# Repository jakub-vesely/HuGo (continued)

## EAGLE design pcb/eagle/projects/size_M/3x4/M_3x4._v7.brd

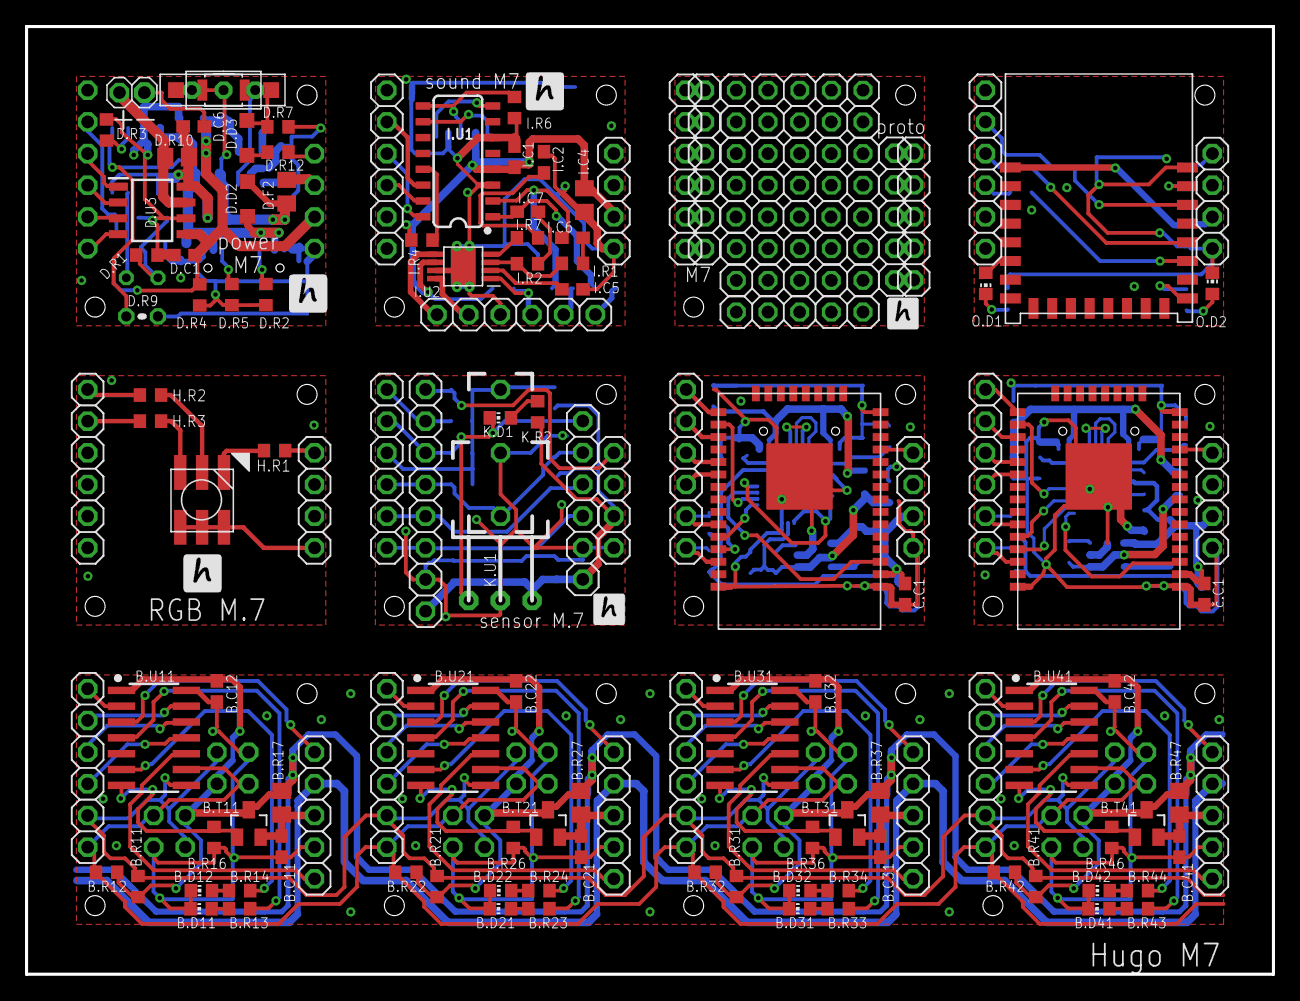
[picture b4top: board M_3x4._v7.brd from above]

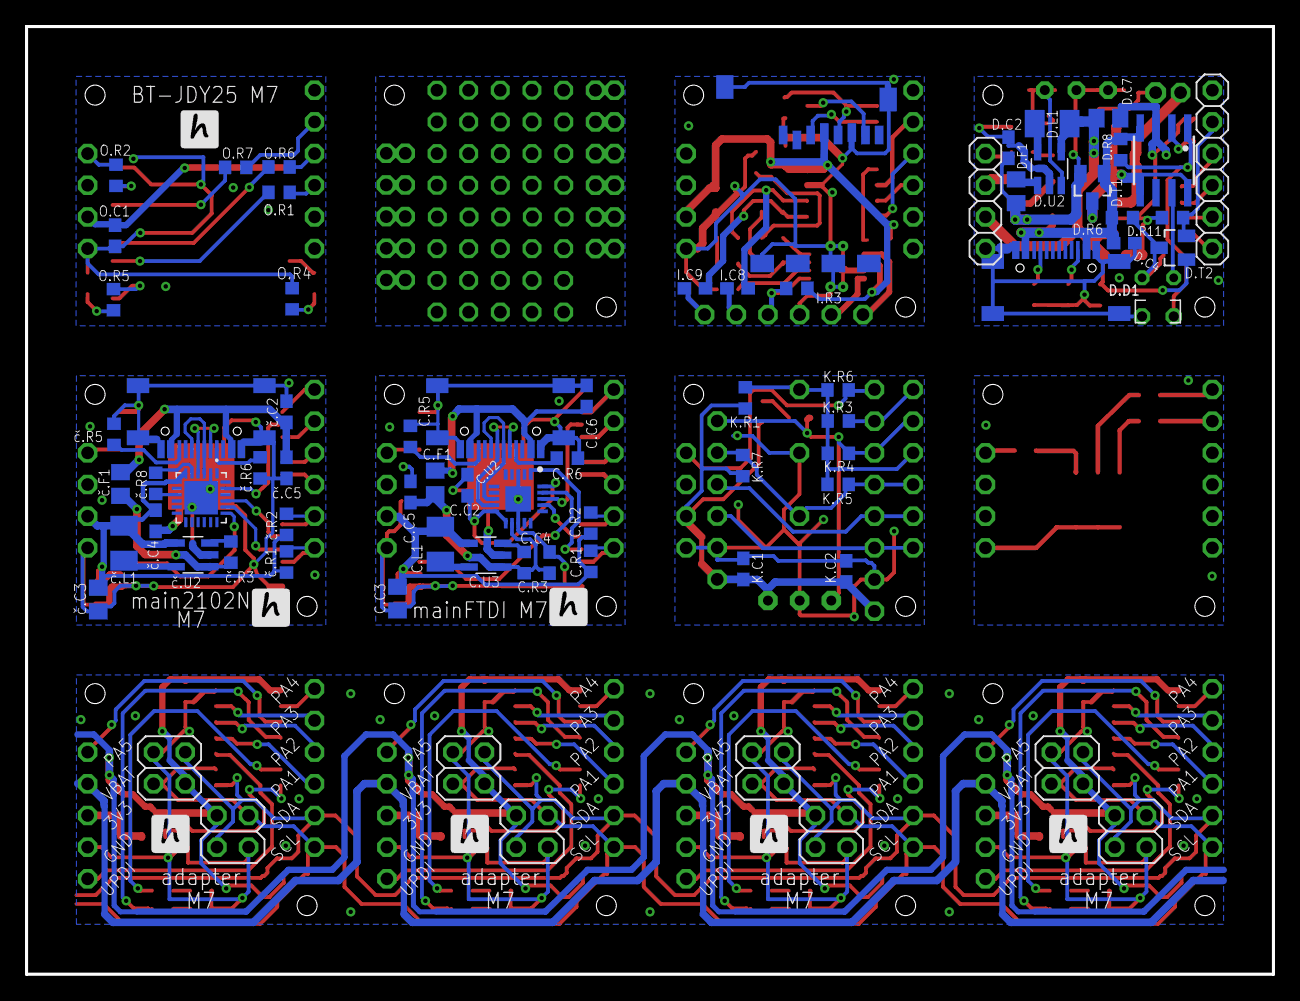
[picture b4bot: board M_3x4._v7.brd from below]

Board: 2 copper layers, 100.0 x 76.0 mm, 201 parts (73 on the bottom side), 185 nets.

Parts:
B.C11, B.C12, B.C21, B.C22, B.C31, B.C32, B.C41, B.C42: 100n; C0603
B.D11, B.D12, B.D21, B.D22, B.D31, B.D32, B.D41, B.D42: CHIP-LED0603
B.J1, B.J8, B.J12, B.J16: 1X05
B.J2, B.J5, B.J9, B.J13: 1X06
B.J3, B.J4, B.J6, B.J7, B.J10, B.J11, B.J14, B.J15: 2X02
B.R11, B.R12, B.R21, B.R22, B.R31, B.R32, B.R41, B.R42: 2k2; R0603
B.R13, B.R14, B.R23, B.R24, B.R33, B.R34, B.R43, B.R44: 1k; R0603
B.R16, B.R26, B.R36, B.R46: 100k; R0603
B.R17, B.R27, B.R37, B.R47: alt fuse or 0R; FUSE
B.T11, B.T21, B.T31, B.T41: NX3008; SO23
B.U11, B.U21, B.U31, B.U41: AT414; SO14
C.C1, C.C2, C.C4: 100n; C0603
C.C3: 22u; C0805
C.C5: 4u7; C0603
C.C6: 10nF; C0603
C.F1: 0.5A; R0805
C.J1, C.J2: 1X06
C.L1: 4u7; L3230M
C.R1, C.R2: 2k2; R0603
C.R3: 100k; R0603
C.R5: 5K1; R0603
C.R6: 5k1; R0603
C.U1, C.U4: TTGO-MICRO-32
C.U2: FT231XQ-R; QFN50P400X400X80-21N
C.U3: MCP1603T-330I; SOT32-5
D.C1: 100n; C0603
D.C2, D.C4, D.C6: 4u7; C0603
D.C7: 10u; C0805
D.D1: LED_1.8
D.D2, D.D3: SHOTKY_2.8
D.F1: 0.5A; R0805
D.F2: 1.1A; R0805
D.J2: 1X06
D.J3: 1X04
D.L1: 2u2; L3230M
D.LIPOL: 1X02-2
D.ON/OFF/RESET: SWITCH
D.R1, D.R2, D.R5: 5k1; R0603
D.R3: I=1800/R (10k for 0.2A, 3k3 for 0.55A, 3k9 for 0.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; R0603
D.R4, D.R7, D.R11: 390k; R0603
D.R6: 3k3; R0603
D.R8: 10k?; R0603
D.R9: TERM_10K; THERM
D.R10: 0.1; R0805
D.R12: 100k; R0603
D.T1: FDV304; SO23
D.T2: NX3008; SO23
D.U2: LM3671_3.3; SOT32-5
D.U3: INA219AIDR; SOIC127P600X175-8N
G.J1: 1X06
G.J2: 1X04
H.D1: RGB_WW-FCE50TC-Q1
H.J2, H.J4: 1X06
H.R1, H.R2, H.R3: 82; R0603
I.C1, I.C2, I.C6, I.C7, I.C8, I.C9: 100n; C0603
I.C4: 10u (22u); C0805
I.C5: 220n; C0603
I.J1, I.J3: 1X04
I.J2: 1X06
I.R1, I.R2, I.R3, I.R4, I.R7: 10k; R0603
I.R6: 1k5; R0603
I.U1: WT2003S; SO16
I.U2: TPA6211; MSOP-POWERPAD-8
JP1, JP2, JP3: 1X04
JP4, JP5, JP7, JP9: 1X06
JP6, JP11: 1X05
JP8: 1X08
K.C1, K.C2: C0603
K.D1: CHIP-LED0603
K.R1, K.R7: 100K; R0603
K.R2: 180R; R0603
K.R3, K.R4, K.R5, K.R6: 0R; R0603
K.U1: VS1838B; IR_RECEIVER
O.C1: 100n; C0603
O.D1, O.D2: CHIP-LED0603
O.R1, O.R2, O.R4, O.R5, O.R6, O.R7: 2k2; R0603
U$1, U$2, U$3: USB-C
U$4: CN3083; SOP8
U$5: MICRO_SD; MOCRO_SD
U$6, U$7, U$8, U$9, U$10, U$11, U$12, U$13: PINHD-1X5_AUTO; 1X5_AUTO
U$14: JDY-25
U$15: BUTTON-SWITCH
č.C1, č.C2, č.C4: 100n; C0603
č.C3: 22u; C0805
č.C5: 4u7; C0603
č.F1: 0.5A; R0805
č.L1: 4u7; L3230M
č.R1, č.R2: 2k2; R0603
č.R3, č.R8: 100k; R0603
č.R5: 5K1; R0603
č.R6: 5k1; R0603
č.U1: CP2102N; QFN50P400X400X80-25N
č.U2: MCP1603T-330I; SOT32-5

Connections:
GND: B.C11.2, B.C12.2, B.C21.2, B.C22.2, B.C31.2, B.C32.2, B.C41.2, B.C42.2, B.D11.C1, B.D12.C1, B.D21.C1, B.D22.C1, B.D31.C1, B.D32.C1, B.D41.C1, B.D42.C1, B.J1.4, B.J3.4, B.J4.1, B.J6.4, B.J7.1, B.J8.4, B.J10.4, B.J11.1, B.J12.4, B.J14.4, B.J15.1, B.J16.4, B.R16.2, B.R26.2, B.R36.2, B.R46.2, B.U11.14, B.U21.14, B.U31.14, B.U41.14
GND1: C.C1.2, C.C2.2, C.C3.2, C.C4.2, C.C5.1, C.C6.1, C.R5.1, C.R6.1, C.U1.GND1, C.U1.GND2, C.U1.GND3, C.U1.GND4, C.U1.GND5, C.U1.GND6, C.U1.GND7, C.U1.GND8, C.U1.GND9, C.U1.GND10, C.U1.GND11, C.U2.3, C.U2.13, C.U2.21, C.U3.GND, JP1.4, U$1.A1B12, U$1.B1A12, U$1.SH1, U$1.SH2, U$1.SH3, U$1.SH4
GND2: C.U4.GND1, C.U4.GND2, C.U4.GND3, C.U4.GND4, C.U4.GND5, C.U4.GND6, C.U4.GND7, C.U4.GND8, C.U4.GND9, C.U4.GND10, C.U4.GND11, JP2.4, U$2.A1B12, U$2.B1A12, U$2.SH1, U$2.SH2, U$2.SH3, U$2.SH4, č.C1.2, č.C2.2, č.C3.2, č.C4.2, č.C5.1, č.R5.1, č.R6.1, č.U1.2, č.U1.25, č.U2.GND
GND3: D.C1.1, D.C2.1, D.C4.1, D.C6.1, D.C7.1, D.J3.4, D.LIPOL.1, D.R1.1, D.R2.2, D.R3.1, D.R4.2, D.R5.2, D.R7.2, D.R9.1, D.R11.2, D.U2.GND, D.U3.6, U$3.A1B12, U$3.B1A12, U$3.SH1, U$3.SH2, U$3.SH3, U$3.SH4, U$4.3
GND4: H.D1.4, H.D1.5, H.D1.6, JP3.4
GND5: H.J4.4, I.C1.2, I.C2.1, I.C4.1, I.C5.1, I.J3.4, I.R6.1, I.U1.3, I.U1.6, I.U2.7, I.U2.9, I.U2.P$10, I.U2.P$11, I.U2.P$12, I.U2.P$13, U$5.6, U$5.G1, U$5.G2, U$5.G3, U$5.G4
GND6: JP6.4, JP11.4
GND7: G.J2.4, O.C1.1, O.D2.C1, O.R4.1, U$14.GND
GND8: I.J1.4, JP8.2, JP9.2, K.C1.2, K.C2.2, K.U1.GND, U$15.P$2
IN+: D.LIPOL.2, D.R10.2, D.U3.7
IN-: D.C6.2, D.R10.1, D.T1.D, D.U3.8, U$4.5, U$4.8
unnamed: B.C21.1, B.J8.3, B.R27.1, B.T21.S
unnamed: B.D22.A1, B.R24.1
unnamed: B.D12.A1, B.R14.1
unnamed: B.C11.1, B.J1.3, B.R17.1, B.T11.S
unnamed: B.R13.2, B.U11.4
unnamed: B.R23.2, B.U21.4
unnamed: B.C31.1, B.J12.3, B.R37.1, B.T31.S
unnamed: B.D32.A1, B.R34.1
unnamed: B.R33.2, B.U31.4
unnamed: B.C41.1, B.J16.3, B.R47.1, B.T41.S
unnamed: B.D42.A1, B.R44.1
unnamed: B.R43.2, B.U41.4
unnamed: C.U2.9, U$1.A7, U$1.B7
unnamed: C.U2.8, U$1.A6, U$1.B6
unnamed: C.R6.2, U$1.A5
unnamed: C.R5.2, U$1.B5
unnamed: C.L1.1, C.U3.VOUT
unnamed: C.R3.1, C.U3.SHDN
unnamed: C.C2.1, C.U2.10, C.U2.11, C.U2.20
unnamed: C.C6.2, C.F1.1, U$1.A4B9, U$1.B4A9
unnamed: U$2.A7, U$2.B7, č.U1.4
unnamed: U$2.A6, U$2.B6, č.U1.3
unnamed: U$2.A5, č.R6.2
unnamed: U$2.B5, č.R5.2
unnamed: č.R8.2, č.U1.5
unnamed: č.L1.1, č.U2.VOUT
unnamed: č.R3.1, č.U2.SHDN
unnamed: C.J1.5, C.U4.IO4
unnamed: C.J1.4, C.U4.IO17
unnamed: C.J1.3, C.U4.IO5
unnamed: C.J1.6, C.U4.IO2
unnamed: C.U4.IO27, JP2.1
unnamed: č.R8.1, č.U1.9
unnamed: č.F1.2, č.R3.2, č.U2.VIN
unnamed: D.L1.1, D.U2.VOUT
unnamed: D.R5.1, U$3.B5
unnamed: D.R2.1, U$3.A5
unnamed: D.R3.2, U$4.2
unnamed: D.D1.1, U$4.7
unnamed: D.R8.1, D.R9.2, U$4.1
unnamed: D.F1.2, D.U2.VIN
unnamed: D.D3.K, D.ON/OFF/RESET.P$1, D.ON/OFF/RESET.P$5, D.ON/OFF/RESET.P$7, D.R7.1, D.U2.SHDN
unnamed: D.D3.A, D.R12.2
unnamed: H.D1.2, H.R2.2
unnamed: H.D1.1, H.R1.2
unnamed: H.D1.3, H.R3.2
unnamed: H.R1.1, JP3.1
unnamed: H.J2.6, H.R2.1
unnamed: H.J2.5, H.R3.1
unnamed: I.C6.1, I.C8.1, I.U1.2
unnamed: I.C7.1, I.C9.1, I.U1.1
unnamed: I.C5.2, I.U2.2
unnamed: I.R1.2, I.R2.2, I.U2.3
unnamed: I.C6.2, I.R1.1
unnamed: I.C7.2, I.R2.1
unnamed: I.C2.2, I.R7.1
unnamed: I.R7.2, I.U2.4
unnamed: I.R4.2, I.U1.13
unnamed: I.J2.5, I.U1.14
unnamed: JP4.5, JP5.5
unnamed: JP4.4, JP5.4
unnamed: JP4.3, JP5.3
unnamed: JP4.2, JP5.2
unnamed: JP4.1, JP5.1
unnamed: JP6.5, JP11.5
unnamed: JP6.2, JP11.2
unnamed: JP6.1, JP11.1
unnamed: JP6.3, JP11.3
unnamed: JP4.6, JP5.6
unnamed: G.J2.1, O.R2.1
unnamed: O.R1.1, U$14.RXD
unnamed: O.R6.1, U$14.TXD
unnamed: G.J1.5, O.R7.2
unnamed: O.R7.1, U$14.PWRC
unnamed: O.D2.A1, O.R5.1
unnamed: O.R5.2, U$14.ALED
unnamed: O.D1.A1, U$14.STAT
unnamed: O.D1.C1, O.R4.2
unnamed: O.R2.2, U$14.RST
unnamed: JP7.2, JP8.4, JP9.4
unnamed: JP7.1, JP8.3, JP9.3
unnamed: K.D1.A1, K.R2.2
unnamed: JP7.6, JP8.7, K.R3.2
unnamed: I.J1.1, JP8.8, K.R6.2
unnamed: JP7.5, JP8.6, JP9.6, K.D1.C1, K.R4.2, K.U1.OUT
unnamed: JP7.4, K.R1.2, K.R3.1, K.R4.1, K.R5.1, K.R6.1, U$15.P$3
unnamed: JP7.3, JP8.5, JP9.5, K.R5.2, K.R7.2, U$15.P$1
PA1: B.J2.3, B.U11.11
PA2: B.J2.4, B.U11.12
PA3: B.J2.5, B.U11.13
PA3-1: D.J2.5, D.R11.1, D.T2.S
PA4: B.J2.6, B.U11.2
PA5: B.J1.1, B.U11.3
PA5-1: D.J3.1, D.R12.1
PA6: B.J5.5, B.U21.13
PA7: B.J5.4, B.U21.12
PA8: B.D21.A1, B.R23.1
PA9: B.J5.6, B.U21.2
PA10: B.J5.3, B.U21.11
PA11: B.J8.1, B.U21.3
PA12: B.J9.5, B.U31.13
PA13: B.J9.4, B.U31.12
PA14: B.D31.A1, B.R33.1
PA15: B.J9.6, B.U31.2
PA16: B.J9.3, B.U31.11
PA17: B.J12.1, B.U31.3
PA18: B.J13.5, B.U41.13
PA19: B.J13.4, B.U41.12
PA20: B.D41.A1, B.R43.1
PA21: B.J13.6, B.U41.2
PA22: B.J13.3, B.U41.11
PA23: B.J16.1, B.U41.3
PA24: C.J2.5, C.U1.IO4
PA25: C.J2.4, C.U1.IO17
PA26: C.J2.3, C.U1.IO5
PA27: C.J2.6, C.U1.IO2
PA28: C.U1.IO27, JP1.1
PA29: D.C4.2, D.D2.A, D.R6.2, D.R8.2, D.T1.G, U$3.A4B9, U$3.B4A9, U$4.4
PA30: D.J2.4, D.U3.1
PA31: D.J2.3, D.U3.2
PA32: D.D1.2, D.R1.2, D.R6.1, D.T2.D
PA51: B.D11.A1, B.R13.1
PB1: B.R26.1, B.T21.G, B.U21.7
PB2: B.R16.1, B.T11.G, B.U11.7
PB3: B.R14.2, B.U11.6
PB4: B.R24.2, B.U21.6
PB5: B.R36.1, B.T31.G, B.U31.7
PB6: B.R34.2, B.U31.6
PB7: B.R46.1, B.T41.G, B.U41.7
PB8: B.R44.2, B.U41.6
PROG: C.U1.IO0, C.U2.18
PROG1: C.U4.IO0, č.U1.23
RESET: C.U1.EN, C.U2.19
RESET1: C.U4.EN, č.U1.19
RX: C.U4.TXD0, č.U1.20
RX1: I.J2.3, I.U1.15
RX2: G.J1.3, O.R6.2
RX/TX: C.U1.TXD0, C.U2.1
SCL: B.J2.1, B.J3.2, B.J4.3, B.J5.1, B.J6.2, B.J7.3, B.J9.1, B.J10.2, B.J11.3, B.J13.1, B.J14.2, B.J15.3, B.R12.1, B.R22.1, B.R32.1, B.R42.1, B.U11.9, B.U21.9, B.U31.9, B.U41.9
SCL1: C.J2.1, C.R1.1, C.U1.IO22
SCL2: C.J1.1, C.U4.IO22, č.R1.1
SCL3: D.J2.1, D.U3.4
SDA: B.J2.2, B.J3.3, B.J4.2, B.J5.2, B.J6.3, B.J7.2, B.J9.2, B.J10.3, B.J11.2, B.J13.2, B.J14.3, B.J15.2, B.R11.1, B.R21.1, B.R31.1, B.R41.1, B.U11.8, B.U21.8, B.U31.8, B.U41.8
SDA1: C.J2.2, C.R2.1, C.U1.IO21
SDA2: C.J1.2, C.U4.IO21, č.R2.1
SDA3: D.J2.2, D.U3.3
SDCLK: I.R6.2, I.U1.9, U$5.5
SDCMD: I.U1.10, U$5.3
SDDAT: I.U1.8, U$5.7
SHTDOWN: H.J4.3, I.R3.1, I.U2.1
TX: C.U4.RXD0, č.U1.21
TX1: I.J2.4, I.U1.16
TX2: G.J1.4, O.R1.2
TX/RX: C.U1.RXD0, C.U2.17
UPDI: B.J1.5, B.U11.10
UPDI1: B.J8.5, B.U21.10
UPDI2: B.J12.5, B.U31.10
UPDI3: B.J16.5, B.U41.10
VBAT: B.J1.2, B.J8.2, B.J12.2, B.J16.2
VBATF: D.F2.2, D.J3.2
VCC: B.C12.1, B.C22.1, B.C32.1, B.C42.1, B.J3.1, B.J4.4, B.J6.1, B.J7.4, B.J10.1, B.J11.4, B.J14.1, B.J15.4, B.R11.2, B.R12.2, B.R17.2, B.R21.2, B.R22.2, B.R27.2, B.R31.2, B.R32.2, B.R37.2, B.R41.2, B.R42.2, B.R47.2, B.T11.D, B.T21.D, B.T31.D, B.T41.D, B.U11.1, B.U21.1, B.U31.1, B.U41.1
VCC1: C.C1.1, C.C3.1, C.L1.2, C.R1.2, C.R2.2, C.U1.3V3, C.U3.BP, JP1.3
VCC2: C.U4.3V3, JP2.3, č.C1.1, č.C3.1, č.C4.1, č.L1.2, č.R1.2, č.R2.2, č.U1.6, č.U1.7, č.U2.BP
VCC3: D.C1.2, D.C7.2, D.J3.3, D.L1.2, D.R4.1, D.T2.G, D.U2.BP, D.U3.5
VCC4: I.C1.1, I.C4.2, I.J3.3, I.R3.2, I.R4.1, I.U1.4, I.U2.6, U$5.4
VCC5: G.J2.3, O.C1.2, U$14.VCC
VCC6: I.J1.3, JP8.1, JP9.1, K.C1.1, K.C2.1, K.R1.1, K.R2.1, K.R7.1, K.U1.VCC
VMOT: D.C2.2, D.D2.K, D.F1.1, D.F2.1, D.ON/OFF/RESET.P$2, D.ON/OFF/RESET.P$3, D.ON/OFF/RESET.P$4, D.ON/OFF/RESET.P$6, D.T1.S
VO+: H.J4.6, I.U2.5
VO-: H.J4.5, I.U2.8
VOUTL: H.J4.1, I.C9.2
VOUTR: H.J4.2, I.C8.2
VUSB: C.C4.1, C.C5.2, C.F1.2, C.R3.2, C.U2.12, C.U3.VIN
VUSB1: U$2.A4B9, U$2.B4A9, č.C2.1, č.C5.2, č.F1.1

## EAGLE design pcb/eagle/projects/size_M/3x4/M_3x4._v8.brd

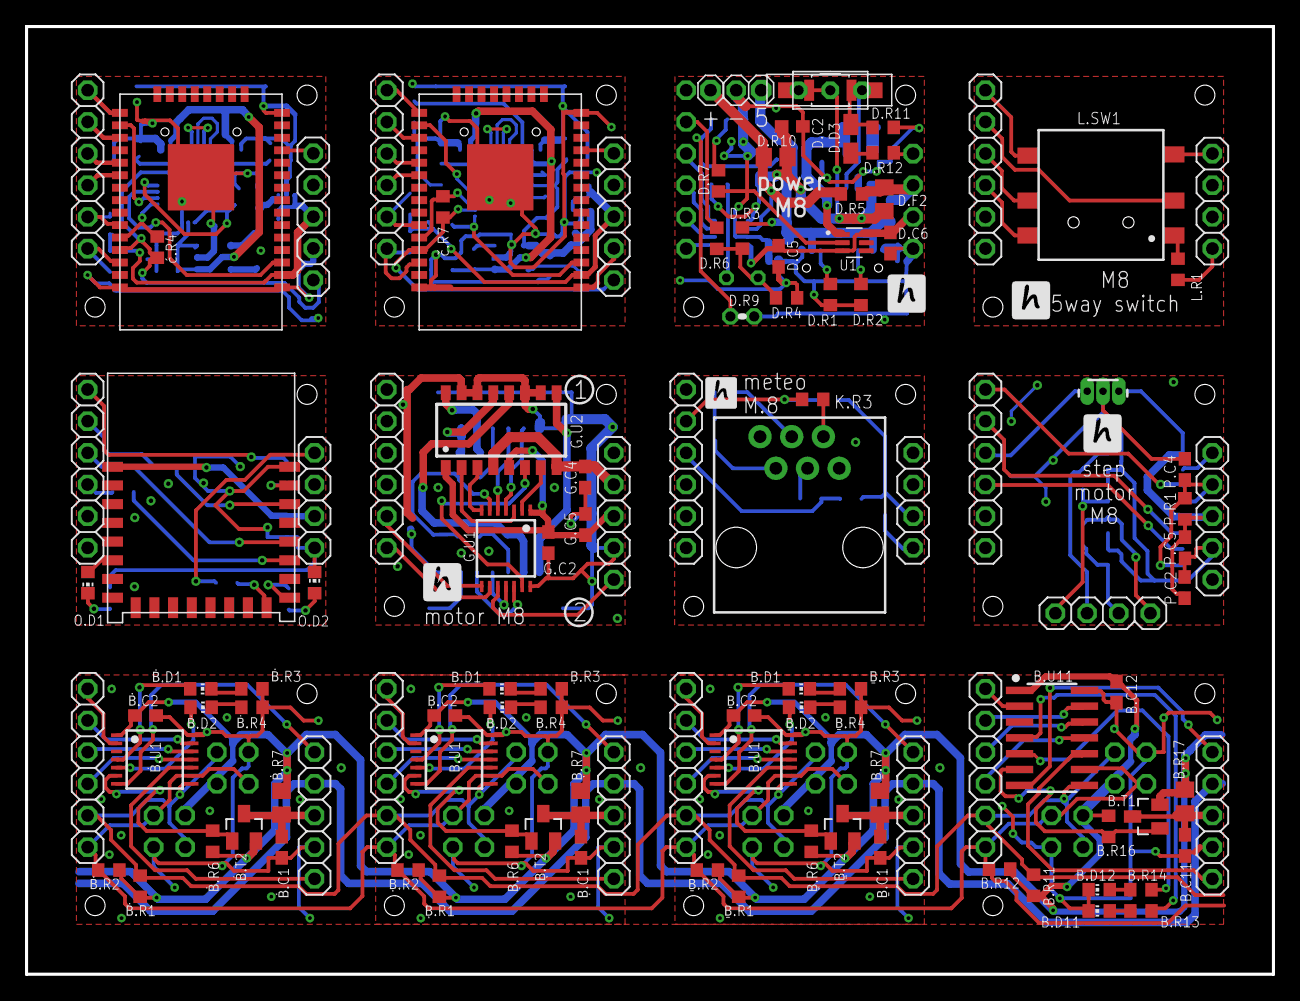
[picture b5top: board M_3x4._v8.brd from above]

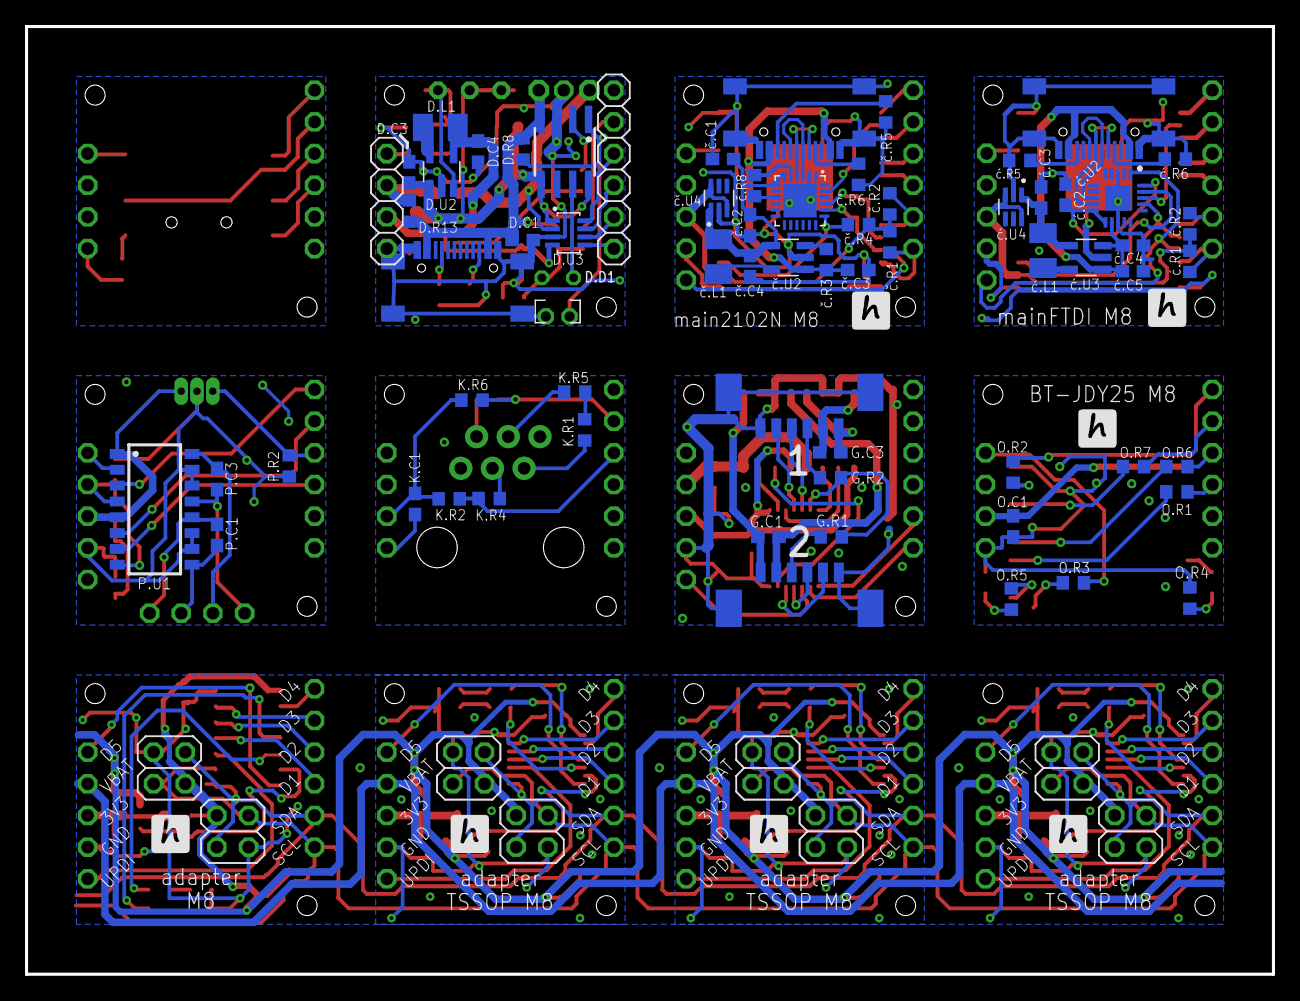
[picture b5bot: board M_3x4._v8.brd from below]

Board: 2 copper layers, 100.0 x 76.0 mm, 185 parts (74 on the bottom side), 183 nets.

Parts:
B.C11, B.C12: 100n; C0603
B.D11: RED; CHIP-LED0603
B.D12: GREEN; CHIP-LED0603
B.J1, B.J8, B.J12, B.J16: 1X05
B.J2, B.J5, B.J9, B.J13: 1X06
B.J3, B.J4, B.J6, B.J7, B.J10, B.J11, B.J14, B.J15: 2X02
B.R11, B.R12, B.R14: 2k2; R0603
B.R13: 330; R0603
B.R16: 100k; R0603
B.R17: alt fuse or 0R; FUSE
B.T1: FDV304; SO23
B.U11: AT414; SO14
C.J1, C.J2: 1X06
D.C1, D.C2, D.C3: 4u7; C0603
D.C4: 10u; C0603
D.C5, D.C6: 100n; C0603
D.D1: LED_1.8
D.D3: SHOTKY_2.8
D.F2: 1.1A; R0805
D.J2: 1X06
D.J3: 1X04
D.L1: 2u2; L3230M
D.LIPOL: PINHEAD-1X3-2; 1X-03-2
D.ON/OFF/RESET: SWITCH
D.R1, D.R2, D.R4: 5k1; R0603
D.R3: 3k3; R0603
D.R5, D.R13: 0; R0603
D.R6, D.R8: 10k; R0603
D.R7: I=1800/R; R0603
D.R9: TERM_10K; THERM
D.R10: 0.1; R0805
D.R11: 390k; R0603
D.R12: 100k; R0603
D.U1: CN3083; SOP8
D.U2: LM3671_3.3; SOT32-5
D.U3: SOT23-8
G.C1, G.C2, G.C3: 100n; C0603
G.C4, G.C5: 4u7; C0603
G.J1, G.J3, G.J5, G.J8: 1X06
G.J2, G.J9: 1X04
G.J4, G.J6: 1X05
G.J7, G.MOTO1: A1250WR-6
G.R1, G.R2: 100; R0603
G.U1: ATTINY3224-XU; TSSOP14
G.U2: MX1508; SOP16
I.J3: 1X04
J1: RJ11; RJ11-6
JP1, JP2: 1X05
JP3: 1X04
JP5: 1X06
K.C1: 100n; C0603
K.R1, K.R3, K.R4, K.R5: 100; R0603
K.R2, K.R6: 10k; R0603
L.R1: 2k2; R0603
L.SW1: 5_WAY_SWITCH
O.C1: 100n; C0603
O.D1, O.D2: CHIP-LED0603
O.R1, O.R2, O.R3, O.R4, O.R5, O.R6, O.R7: 2k2; R0603
P.C1, P.C2, P.C3: 100n; C0603
P.C4, P.C5: 4u7; C0603
P.R1, P.R2: 0 (alt); R0603
P.U1: MX1508; SOP16
P.U2: A1202UA; SIP3-UA
U1: LM66100DCKR; SOT65P210X110-6N
U$1, U$2, U$3: USB-C
U$4: JDY-25
ć.C2, ć.C4: 100n; C0603
ć.C3: 10u; C0603
ć.C5: 4u7; C0603
ć.L1: 2u2; L3230M
ć.R1, ć.R2, ć.R4: 2k2; R0603
ć.R5: 5K1; R0603
ć.R6: 5k1; R0603
ć.U1: TTGO-MICRO-32
ć.U2: FT231XQ-R; QFN50P400X400X80-21N
ć.U3: LM3671_3.3; SOT32-5
ć.U4: LM66100DCKR; SOT65P210X110-6N
č.C1: 100n; C0603
č.C2: 4u7; C0603
č.C3: 4k7; C0603
č.C4: 10u; C0603
č.L1: 2u2; L3230M
č.R1, č.R2: 2k2; R0603
č.R3, č.R4: 100k; R0603
č.R5: 5K1; R0603
č.R6: 5k1; R0603
č.R7: 4k7; R0603
č.R8: 1k; R0603
č.U1: CP2102N; QFN50P400X400X80-25N
č.U2: LM3671_3.3; SOT32-5
č.U3: TTGO-MICRO-32
č.U4: LM66100DCKR; SOT65P210X110-6N
Ḃ.C1, Ḃ.C2: 100n; C0603
Ḃ.D1: RED; CHIP-LED0603
Ḃ.D2: GREEN; CHIP-LED0603
Ḃ.R1, Ḃ.R2, Ḃ.R4: 2k2; R0603
Ḃ.R3: 330; R0603
Ḃ.R6: 100k; R0603
Ḃ.R7: alt fuse or 0R; FUSE
Ḃ.T2: FDV304; SO23
Ḃ.U1: ATTINY3224-XU; TSSOP14
Ḅ.C1, Ḅ.C2: 100n; C0603
Ḅ.D1: RED; CHIP-LED0603
Ḅ.D2: GREEN; CHIP-LED0603
Ḅ.R1, Ḅ.R2, Ḅ.R4: 2k2; R0603
Ḅ.R3: 330; R0603
Ḅ.R6: 100k; R0603
Ḅ.R7: alt fuse or 0R; FUSE
Ḅ.T2: FDV304; SO23
Ḅ.U1: ATTINY3224-XU; TSSOP14
Ḇ.C1, Ḇ.C2: 100n; C0603
Ḇ.D1: RED; CHIP-LED0603
Ḇ.D2: GREEN; CHIP-LED0603
Ḇ.R1, Ḇ.R2, Ḇ.R4: 2k2; R0603
Ḇ.R3: 330; R0603
Ḇ.R6: 100k; R0603
Ḇ.R7: alt fuse or 0R; FUSE
Ḇ.T2: FDV304; SO23
Ḇ.U1: ATTINY3224-XU; TSSOP14

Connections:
5V: D.C1.2, D.LIPOL.1, D.R3.2, D.R8.2, D.R13.1, D.U1.4, U$3.A4B9, U$3.B4A9
CENTER: G.J2.1, L.SW1.3
CHRG: D.D1.2, D.R3.1, D.R4.2, D.R6.1
COMMON: L.R1.1, L.SW1.1
DOWN: G.J1.6, L.SW1.6
FOTOB1: G.MOTO1.4, G.U1.5
FOTOB2: G.J7.4, G.U1.11
GND: JP1.4, U$1.A1B12, U$1.B1A12, U$1.SH1, U$1.SH2, U$1.SH3, U$1.SH4, č.C1.1, č.C2.2, č.C3.1, č.C4.2, č.R5.1, č.R6.1, č.U1.2, č.U1.25, č.U2.GND, č.U3.GND1, č.U3.GND2, č.U3.GND3, č.U3.GND4, č.U3.GND5, č.U3.GND6, č.U3.GND7, č.U3.GND8, č.U3.GND9, č.U3.GND10, č.U3.GND11, č.U4.2
GND1: JP2.4, U$2.A1B12, U$2.B1A12, U$2.SH1, U$2.SH2, U$2.SH3, U$2.SH4, ć.C2.2, ć.C3.2, ć.C4.2, ć.C5.1, ć.R5.1, ć.R6.1, ć.U1.GND1, ć.U1.GND2, ć.U1.GND3, ć.U1.GND4, ć.U1.GND5, ć.U1.GND6, ć.U1.GND7, ć.U1.GND8, ć.U1.GND9, ć.U1.GND10, ć.U1.GND11, ć.U2.3, ć.U2.13, ć.U2.21, ć.U3.GND, ć.U4.2
GND2: B.C11.2, B.C12.2, B.D11.C1, B.D12.C1, B.J1.4, B.J3.4, B.J4.1, B.J6.4, B.J7.1, B.J8.4, B.J10.4, B.J11.1, B.J12.4, B.J14.4, B.J15.1, B.J16.4, B.U11.14, Ḃ.C1.2, Ḃ.C2.2, Ḃ.R3.1, Ḃ.R4.1, Ḃ.U1.14, Ḅ.C1.2, Ḅ.C2.2, Ḅ.R3.1, Ḅ.R4.1, Ḅ.U1.14, Ḇ.C1.2, Ḇ.C2.2, Ḇ.R3.1, Ḇ.R4.1, Ḇ.U1.14
GND3: G.J9.4, O.C1.1, O.D2.C1, O.R4.1, U$4.GND
GND4: D.C1.1, D.C2.1, D.C3.1, D.C4.1, D.C5.1, D.C6.1, D.J3.4, D.LIPOL.2, D.R1.2, D.R2.2, D.R4.1, D.R7.1, D.R9.1, D.R11.2, D.U1.3, D.U2.GND, D.U3.3, U1.2, U$3.A1B12, U$3.B1A12, U$3.SH1, U$3.SH2, U$3.SH3, U$3.SH4
GND5: G.J2.4, L.R1.2
GND6: G.J4.4, P.C2.1, P.C4.1, P.C5.1, P.R2.1, P.U1.10, P.U1.11, P.U1.14, P.U1.15, P.U2.2
GND7: G.C2.1, G.C4.1, G.C5.1, G.J6.4, G.J7.6, G.J7.$1, G.J7.$2, G.MOTO1.6, G.MOTO1.$1, G.MOTO1.$2, G.U1.14, G.U2.10, G.U2.11, G.U2.14, G.U2.15
GND9: I.J3.4, K.C1.2, K.R1.1, K.R5.1
IN+: D.C2.2, D.C3.2, D.F2.1, D.ON/OFF/RESET.P$2, D.ON/OFF/RESET.P$3, D.ON/OFF/RESET.P$4, D.ON/OFF/RESET.P$6, D.R10.1, D.U1.5, D.U1.8, D.U2.VIN, D.U3.1
IN-: D.LIPOL.3, D.R5.1, D.R10.2, D.U3.2
INA1: G.J4.1, P.U1.2
INA2: G.J3.5, P.U1.6
INA3: G.U1.13, G.U2.6
INA4: G.U1.3, G.U2.2
INB1: G.J3.6, P.U1.3
INB2: G.J3.3, P.U1.7
INB3: G.U1.7, G.U2.3
INB4: G.U1.2, G.U2.7
LEFT: G.J1.5, L.SW1.2
MA1: JP3.2, P.C3.1, P.U1.16
MA2: JP3.4, P.C1.1, P.U1.12
MA3: G.C3.1, G.MOTO1.2, G.U2.16
MA4: G.C1.1, G.J7.2, G.U2.12
MB1: JP3.1, P.C3.2, P.U1.13
MB2: JP3.3, P.C1.2, P.U1.9
MB3: G.C3.2, G.MOTO1.1, G.U2.13
MB4: G.C1.2, G.J7.1, G.U2.9
M_V: G.J4.2, P.C4.2, P.R1.1, P.U1.4, P.U1.8
M_V1: G.C4.2, G.J6.2, G.U2.4, G.U2.8
unnamed: U$1.A7, U$1.B7, č.U1.4
unnamed: U$1.A6, U$1.B6, č.U1.3
unnamed: U$1.A5, č.R6.2
unnamed: U$1.B5, č.R5.2
unnamed: U$2.A7, U$2.B7, ć.U2.9
unnamed: C.J2.6, č.U3.IO2
unnamed: JP1.1, č.U3.IO27
unnamed: č.R8.2, č.U1.5
unnamed: U$2.A6, U$2.B6, ć.U2.8
unnamed: č.L1.1, č.U2.VOUT
unnamed: č.R3.1, č.U2.SHDN
unnamed: C.J2.5, č.U3.IO4
unnamed: C.J2.4, č.U3.IO17
unnamed: C.J2.3, č.U3.IO5
unnamed: U$2.A5, ć.R6.2
unnamed: č.R8.1, č.U1.9
unnamed: U$2.B5, ć.R5.2
unnamed: ć.L1.1, ć.U3.VOUT
unnamed: ć.C2.1, ć.U2.10, ć.U2.11, ć.U2.20
unnamed: Ḃ.D1.A1, Ḃ.U1.4
unnamed: Ḃ.D2.C1, Ḃ.R4.2
unnamed: Ḃ.D1.C1, Ḃ.R3.2
unnamed: B.J1.3, Ḃ.C1.1, Ḃ.R7.1, Ḃ.T2.D
unnamed: Ḅ.D1.A1, Ḅ.U1.4
unnamed: Ḅ.D2.C1, Ḅ.R4.2
unnamed: Ḅ.D1.C1, Ḅ.R3.2
unnamed: D.L1.1, D.U2.VOUT
unnamed: D.R1.1, U$3.B5
unnamed: D.R2.1, U$3.A5
unnamed: D.R7.2, D.U1.2
unnamed: D.D1.1, D.U1.7
unnamed: D.R8.1, D.R9.2, D.U1.1
unnamed: D.D3.K, D.ON/OFF/RESET.P$1, D.ON/OFF/RESET.P$5, D.ON/OFF/RESET.P$7, D.R11.1, D.U2.SHDN
unnamed: D.D3.A, D.R12.2
unnamed: G.J3.4, P.R2.2, P.U2.3
unnamed: B.J8.3, Ḅ.C1.1, Ḅ.R7.1, Ḅ.T2.D
unnamed: Ḇ.D1.A1, Ḇ.U1.4
unnamed: Ḇ.D2.C1, Ḇ.R4.2
unnamed: Ḇ.D1.C1, Ḇ.R3.2
unnamed: B.J12.3, Ḇ.C1.1, Ḇ.R7.1, Ḇ.T2.D
unnamed: B.C11.1, B.J16.3, B.R17.1, B.T1.D
unnamed: B.D12.A1, B.R14.1
unnamed: B.R13.2, B.U11.4
unnamed: G.J9.1, O.R3.2
unnamed: O.R1.1, U$4.RXD
unnamed: O.R6.1, U$4.TXD
unnamed: G.J8.5, O.R7.2
unnamed: O.R7.1, U$4.PWRC
unnamed: O.D2.A1, O.R5.1
unnamed: O.R5.2, U$4.ALED
unnamed: O.D1.A1, U$4.STAT
unnamed: JP5.5, K.R3.1, K.R6.2
unnamed: JP5.4, K.R2.2, K.R4.1
unnamed: J1.3, K.R5.2
unnamed: J1.2, K.R1.2
unnamed: J1.5, K.R3.2
unnamed: J1.4, K.R4.2
unnamed: O.D1.C1, O.R4.2
unnamed: O.R2.2, U$4.RST
unnamed: G.J8.6, O.R2.1
unnamed: O.R3.1, U$4.OUT1
PA1: C.J1.3, ć.U1.IO5
PA2: C.J1.4, ć.U1.IO17
PA3: C.J1.5, ć.U1.IO4
PA4: C.J1.6, ć.U1.IO2
PA5: JP2.1, ć.U1.IO27
PA5-1: D.J3.1, D.R12.1
PA6: B.J2.5, Ḃ.U1.13
PA7: B.J2.4, Ḃ.U1.12
PA8: B.J2.6, Ḃ.U1.2
PA9: B.J2.3, Ḃ.U1.11
PA10: Ḃ.D2.A1, Ḃ.U1.5
PA11: B.J5.5, Ḅ.U1.13
PA12: B.J5.4, Ḅ.U1.12
PA13: B.J5.6, Ḅ.U1.2
PA14: B.J5.3, Ḅ.U1.11
PA15: Ḅ.D2.A1, Ḅ.U1.5
PA16: B.J9.5, Ḇ.U1.13
PA17: B.J9.4, Ḇ.U1.12
PA18: D.J2.4, D.U3.8
PA19: D.J2.3, D.U3.7
PA20: D.J2.5, D.R6.2
PA21: B.J9.6, Ḇ.U1.2
PA22: B.J9.3, Ḇ.U1.11
PA23: Ḇ.D2.A1, Ḇ.U1.5
PA24: B.J13.5, B.U11.13
PA25: B.J13.4, B.U11.12
PA26: B.J13.6, B.U11.2
PA27: B.J13.3, B.U11.11
PA28: B.R14.2, B.U11.5
PA51: B.D11.A1, B.R13.1
PB1: Ḅ.R6.1, Ḅ.T2.G, Ḅ.U1.6
PB2: B.J1.1, Ḃ.U1.7
PB3: Ḃ.R6.1, Ḃ.T2.G, Ḃ.U1.6
PB4: B.J8.1, Ḅ.U1.7
PB5: Ḇ.R6.1, Ḇ.T2.G, Ḇ.U1.6
PB6: B.J12.1, Ḇ.U1.7
PB7: B.R16.1, B.T1.G, B.U11.6
PB8: B.J16.1, B.U11.7
POWER1: G.MOTO1.3, G.R2.1
POWER2: G.J7.3, G.R1.1
POWER_LED: G.R1.2, G.R2.2, G.U1.6
PROG: č.U1.23, č.U3.IO0
PROG1: ć.U1.IO0, ć.U2.18
RESET: č.R4.1, č.U1.19, č.U3.EN
RESET1: ć.U1.EN, ć.U2.19
RIGHT: G.J1.4, L.SW1.5
RX: JP1.5, č.R7.1, č.U1.20, č.U3.TXD0
RX1: G.J8.3, O.R6.2
RX/TX: JP2.5, ć.R4.1, ć.U1.TXD0, ć.U2.1
SCL: C.J2.1, č.R1.1, č.U3.IO22
SCL1: C.J1.1, ć.R1.1, ć.U1.IO22
SCL2: G.J5.1, G.U1.9
SCL3: B.J2.1, B.J3.2, B.J4.3, B.J5.1, B.J6.2, B.J7.3, B.J9.1, B.J10.2, B.J11.3, B.J13.1, B.J14.2, B.J15.3, B.R12.1, B.U11.9, Ḃ.R2.1, Ḃ.U1.9, Ḅ.R2.1, Ḅ.U1.9, Ḇ.R2.1, Ḇ.U1.9
SCL4: D.J2.1, D.U3.5
SDA: C.J2.2, č.R2.1, č.U3.IO21
SDA1: C.J1.2, ć.R2.1, ć.U1.IO21
SDA2: B.J2.2, B.J3.3, B.J4.2, B.J5.2, B.J6.3, B.J7.2, B.J9.2, B.J10.3, B.J11.2, B.J13.2, B.J14.3, B.J15.2, B.R11.1, B.U11.8, Ḃ.R1.1, Ḃ.U1.8, Ḅ.R1.1, Ḅ.U1.8, Ḇ.R1.1, Ḇ.U1.8
SDA3: G.J5.2, G.U1.8
SDA4: D.J2.2, D.U3.6
TX: č.R7.2, č.U1.21, č.U3.RXD0
TX1: G.J8.4, O.R1.2
TX/RX: ć.R4.2, ć.U1.RXD0, ć.U2.17
UP: G.J1.3, L.SW1.4
UPDI: B.J1.5, Ḃ.U1.10
UPDI1: B.J8.5, Ḅ.U1.10
UPDI2: B.J12.5, Ḇ.U1.10
UPDI3: B.J16.5, B.U11.10
UPDI4: G.J6.5, G.U1.10
VBAT: B.J1.2, B.J8.2, B.J12.2, B.J16.2
VCC: JP1.3, č.R1.2, č.R2.2, č.R4.2, č.U3.3V3, č.U4.3, č.U4.6
VCC1: č.C1.2, č.C2.1, č.C4.1, č.L1.2, č.U1.6, č.U1.7, č.U2.BP, č.U4.1
VCC2: JP2.3, ć.R1.2, ć.R2.2, ć.U1.3V3, ć.U4.3, ć.U4.6
VCC3: ć.C3.1, ć.L1.2, ć.U3.BP, ć.U4.1
VCC4: B.C12.1, B.J3.1, B.J4.4, B.J6.1, B.J7.4, B.J10.1, B.J11.4, B.J14.1, B.J15.4, B.R11.2, B.R12.2, B.R16.2, B.R17.2, B.T1.S, B.U11.1, Ḃ.C2.1, Ḃ.R1.2, Ḃ.R2.2, Ḃ.R6.2, Ḃ.R7.2, Ḃ.T2.S, Ḃ.U1.1, Ḅ.C2.1, Ḅ.R1.2, Ḅ.R2.2, Ḅ.R6.2, Ḅ.R7.2, Ḅ.T2.S, Ḅ.U1.1, Ḇ.C2.1, Ḇ.R1.2, Ḇ.R2.2, Ḇ.R6.2, Ḇ.R7.2, Ḇ.T2.S, Ḇ.U1.1
VCC5: G.J9.3, O.C1.2, U$4.VCC
VCC6: D.C4.2, D.L1.2, D.U2.BP, U1.1
VCC7: D.C5.2, D.C6.2, D.J3.3, D.U3.4, U1.3, U1.6
VCC9: G.J4.3, P.C2.2, P.C5.2, P.R1.2, P.U1.1, P.U1.5, P.U2.1
VCC10: G.C2.2, G.C5.2, G.J6.3, G.U1.1, G.U2.1, G.U2.5
VCC11: I.J3.3, K.C1.1, K.R2.1, K.R6.1
VOPT: D.F2.2, D.J3.2, D.R5.2, D.R13.2
VUSB: U$1.A4B9, U$1.B4A9, č.C3.2, č.R3.2, č.U2.VIN
VUSB1: U$2.A4B9, U$2.B4A9, ć.C4.1, ć.C5.2, ć.U2.12, ć.U3.SHDN, ć.U3.VIN
_FOTOA1_: G.MOTO1.5, G.U1.4
_FOTOA2_: G.J7.5, G.U1.12
